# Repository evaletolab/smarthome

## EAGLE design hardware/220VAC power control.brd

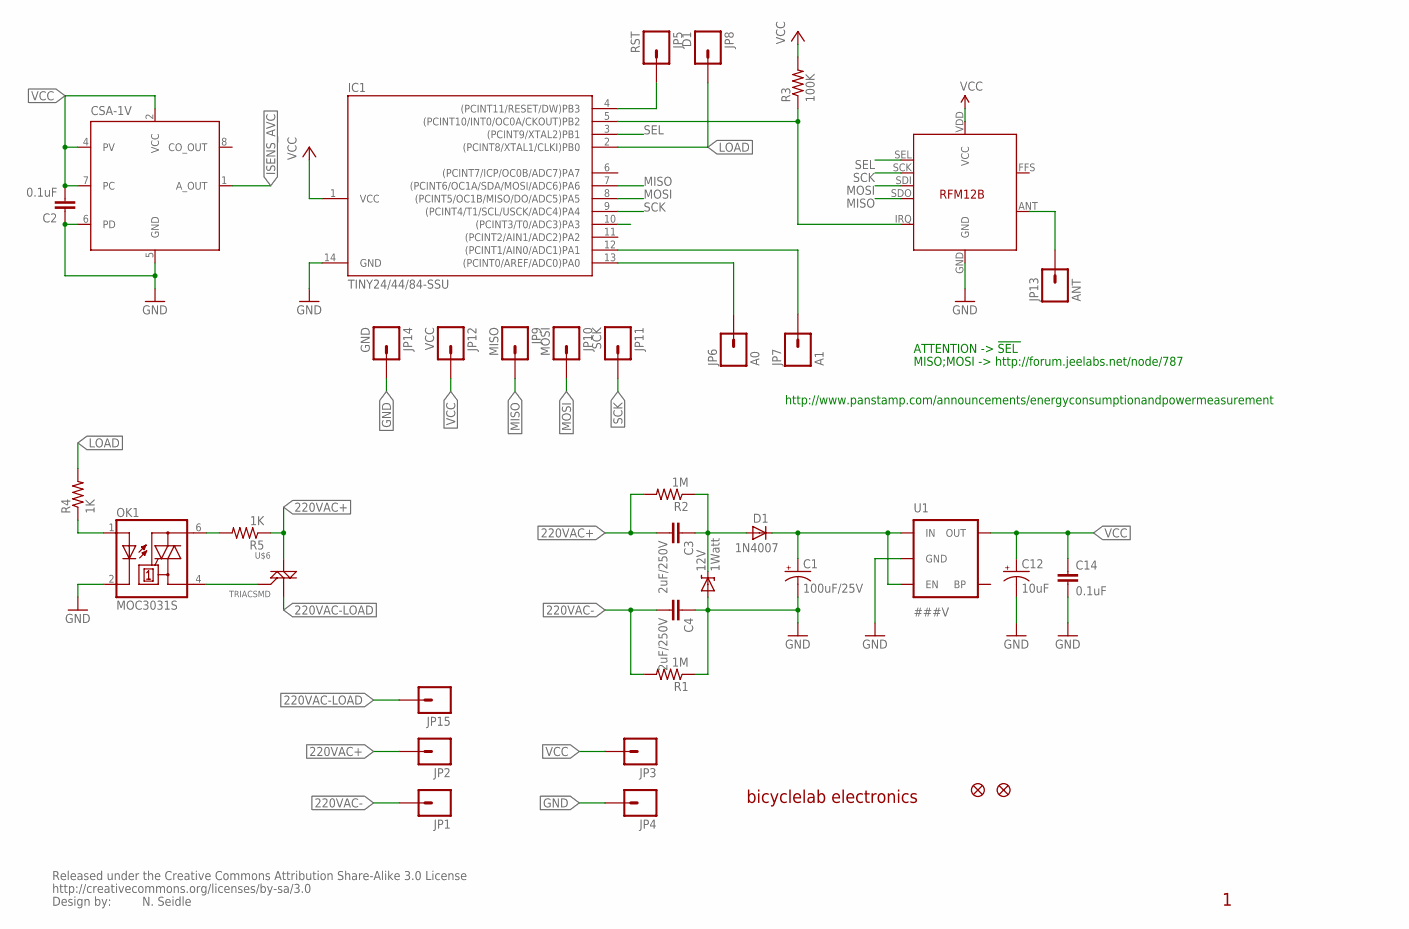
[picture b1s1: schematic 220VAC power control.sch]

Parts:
12V: 1Watt; SMB-DIODE
C1: 100uF/25V; EIA7343
C2, C14: 0.1uF; 0603-CAP
C3, C4: 2uF/250V; 0402-CAP
C12: 10uF; EIA3216
D1: 1N4007; SMA-DIODE
IC1: TINY24/44/84-SSU; SOIC14
JP1, JP2, JP3, JP4, JP15: M01PTH; 1X01
JP5: RST; 1X01_POGOPIN_HOLE_0.58
JP6: A0; 1X01_POGOPIN_HOLE_0.58
JP7: A1; 1X01_POGOPIN_HOLE_0.58
JP8: D1; 1X01_POGOPIN_HOLE_0.58
JP9: MISO; 1X01_POGOPIN_HOLE_0.58
JP10: MOSI; 1X01_POGOPIN_HOLE_0.58
JP11: SCK; 1X01_POGOPIN_HOLE_0.58
JP12: VCC; 1X01_POGOPIN_HOLE_0.58
JP13: ANT; PAD-1.5X4.5
JP14: GND; 1X01NS
OK1: MOC3031S; DIL6-SMD
R1, R2: 1M; 0402-RES
R3: 100K; 0805
R4, R5: 1K; 0805
U1: ###V; SOT23-5
U$1: CSA-1V; SOIC8
U$2: RFM12B
U$3, U$4: FIDUCIAL1X2; FIDUCIAL-1X2
U$5: CREATIVE_COMMONS
U$6: TRIACSMD; SOT223

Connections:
220VAC+: C3.2, JP2.1, R2.2, R5.1, U$6.2 (M2)
220VAC-: C4.2, JP1.1, R1.2
220VAC-LOAD: JP15.1, U$6.1 (M1)
!RESET: IC1.4 ((PCINT11/RESET/DW)PB3), JP5.1
AD1: IC1.13 ((PCINT0/AREF/ADC0)PA0), JP6.1
GND: 12V.A, C1.C (-), C2.1, C4.1, C12.C (-), C14.2, IC1.14 (GND), JP4.1, JP14.1, OK1.2 (C), R1.1, U1.2 (GND), U$1.5 (GND), U$1.6 (PD), U$2.GND
ISENS_AVC: IC1.12 ((PCINT1/AIN0/ADC1)PA1), JP7.1, U$1.1 (A_OUT)
LOAD: IC1.2 ((PCINT8/XTAL1/CLKI)PB0), JP8.1, R4.2
MISO: IC1.7 ((PCINT6/OC1A/SDA/MOSI/ADC6)PA6), JP9.1, U$2.SDO
MOSI: IC1.8 ((PCINT5/OC1B/MISO/DO/ADC5)PA5), JP10.1, U$2.SDI
unnamed: 12V.C, C3.1, D1.A, R2.1
unnamed: IC1.5 ((PCINT10/INT0/OC0A/CKOUT)PB2), R3.1, U$2.IRQ
unnamed: OK1.1 (A), R4.1
unnamed: C1.A (+), D1.C, U1.1 (IN), U1.3 (EN)
unnamed: OK1.6 (A2), R5.2
unnamed: OK1.4 (A1), U$6.3 (G)
unnamed: JP13.P$1, U$2.ANT
SCK: IC1.9 ((PCINT4/T1/SCL/USCK/ADC4)PA4), JP11.1, U$2.SCK
SEL: IC1.3 ((PCINT9/XTAL2)PB1), U$2.SEL
VCC: C2.2, C12.A (+), C14.1, IC1.1 (VCC), JP3.1, JP12.1, R3.2, U1.5 (OUT), U$1.2 (VCC), U$1.4 (PV), U$1.7 (PC), U$2.VDD (VCC)

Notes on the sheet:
bicyclelab electronics
N. Seidle
ATTENTION -> !SEL
MISO;MOSI -> http://forum.jeelabs.net/node/787
http://www.panstamp.com/announcements/energyconsumptionandpowermeasurement

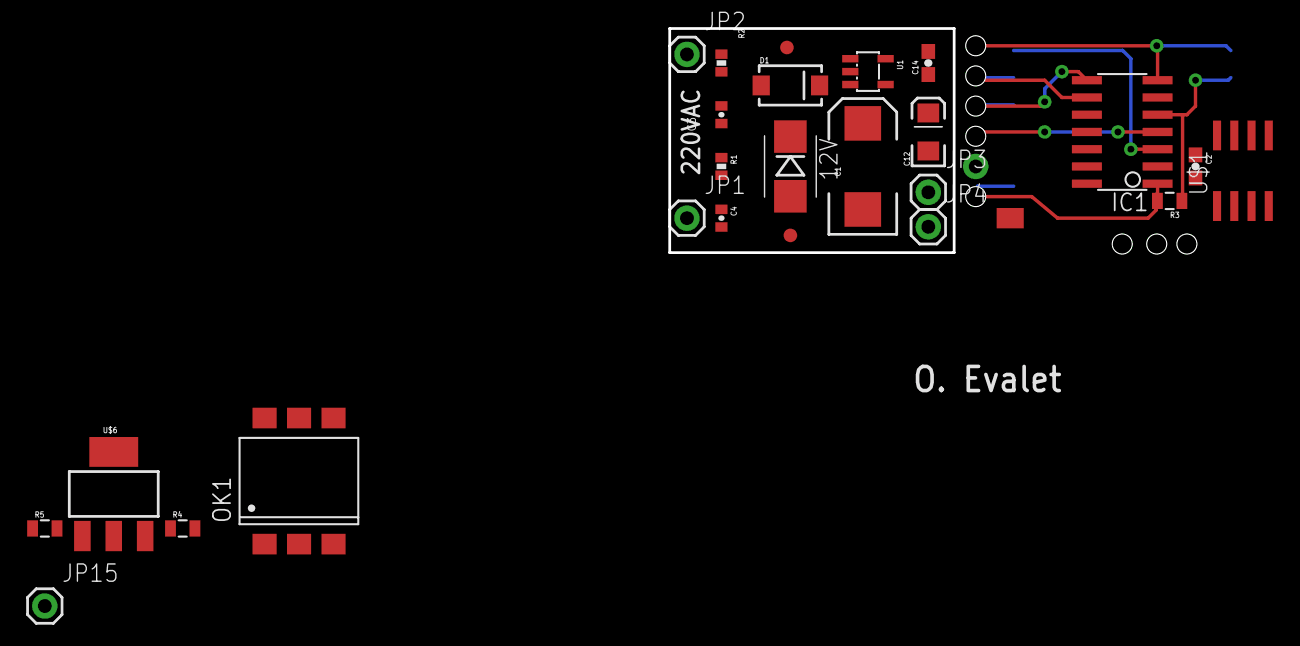
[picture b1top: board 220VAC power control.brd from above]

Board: 2 copper layers, 21.0 x 16.5 mm, 37 parts (1 on the bottom side), 20 nets.

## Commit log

2012-11-04 initial import

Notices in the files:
parts and their libraries:
SparkFun: Released under the Creative Commons Attribution Share-Alike 3.0 License
SparkFun: http://creativecommons.org/licenses/by-sa/3.0
